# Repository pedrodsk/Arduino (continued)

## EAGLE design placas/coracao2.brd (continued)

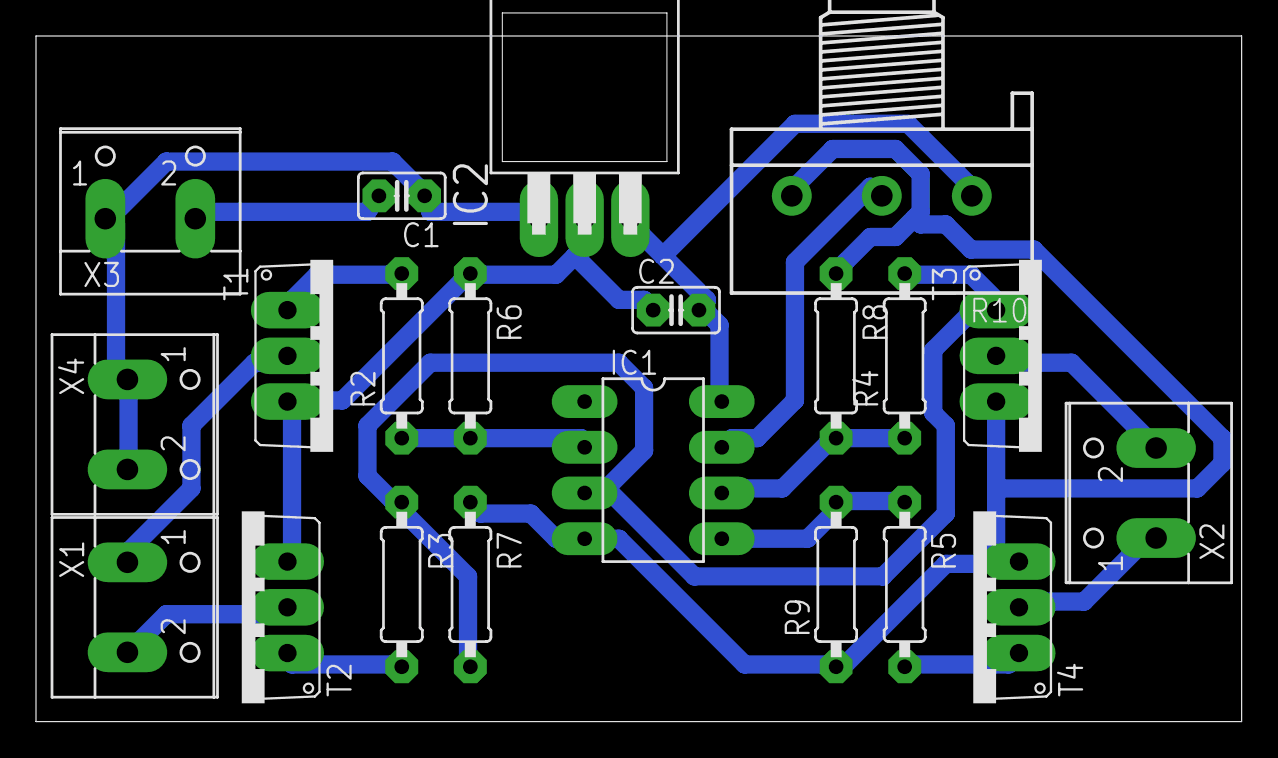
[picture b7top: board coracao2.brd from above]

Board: 1 copper layer, 67.0 x 38.1 mm, 21 parts (0 on the bottom side), 15 nets.

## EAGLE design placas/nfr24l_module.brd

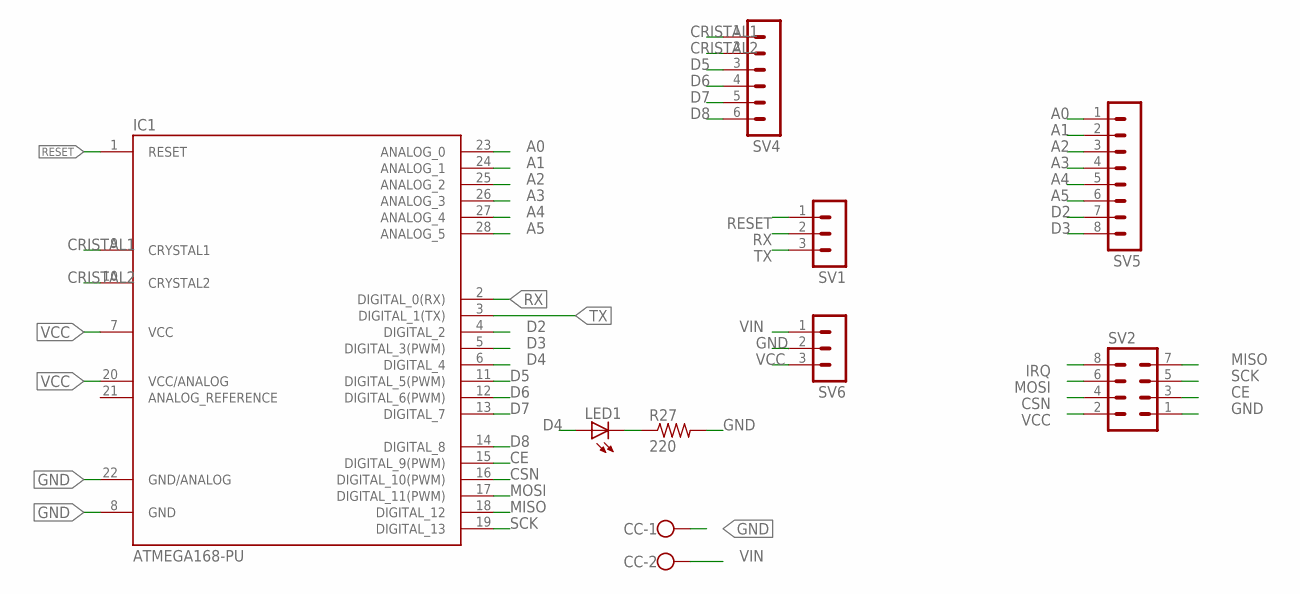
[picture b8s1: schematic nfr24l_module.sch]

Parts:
CC: W237-102
IC1: ATMEGA168-PU; DIL28-3
LED1: LED3MM
R27: 220; 0207/7
SV1, SV6: MA03-1
SV2: MA04-2
SV4: MA06-1
SV5: MA08-1

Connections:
A0: IC1.23 (ANALOG_0), SV5.1
A1: IC1.24 (ANALOG_1), SV5.2
A2: IC1.25 (ANALOG_2), SV5.3
A3: IC1.26 (ANALOG_3), SV5.4
A4: IC1.27 (ANALOG_4), SV5.5
A5: IC1.28 (ANALOG_5), SV5.6
CE: IC1.15 (DIGITAL_9(PWM)), SV2.3
CRISTAL1: IC1.9 (CRYSTAL1), SV4.1
CRISTAL2: IC1.10 (CRYSTAL2), SV4.2
CSN: IC1.16 (DIGITAL_10(PWM)), SV2.4
D2: IC1.4 (DIGITAL_2), SV5.7
D3: IC1.5 (DIGITAL_3(PWM)), SV5.8
D4: IC1.6 (DIGITAL_4), LED1.A
D5: IC1.11 (DIGITAL_5(PWM)), SV4.3
D6: IC1.12 (DIGITAL_6(PWM)), SV4.4
D7: IC1.13 (DIGITAL_7), SV4.5
D8: IC1.14 (DIGITAL_8), SV4.6
GND: CC.1, IC1.8 (GND), IC1.22 (GND/ANALOG), R27.2, SV2.1, SV6.2
IRQ: SV2.8
MISO: IC1.18 (DIGITAL_12), SV2.7
MOSI: IC1.17 (DIGITAL_11(PWM)), SV2.6
unnamed: LED1.K (C), R27.1
RESET: IC1.1 (RESET), SV1.1
RX: IC1.2 (DIGITAL_0(RX)), SV1.2
SCK: IC1.19 (DIGITAL_13), SV2.5
TX: IC1.3 (DIGITAL_1(TX)), SV1.3
VCC: IC1.7 (VCC), IC1.20 (VCC/ANALOG), SV2.2, SV6.3
VIN: CC.2, SV6.1

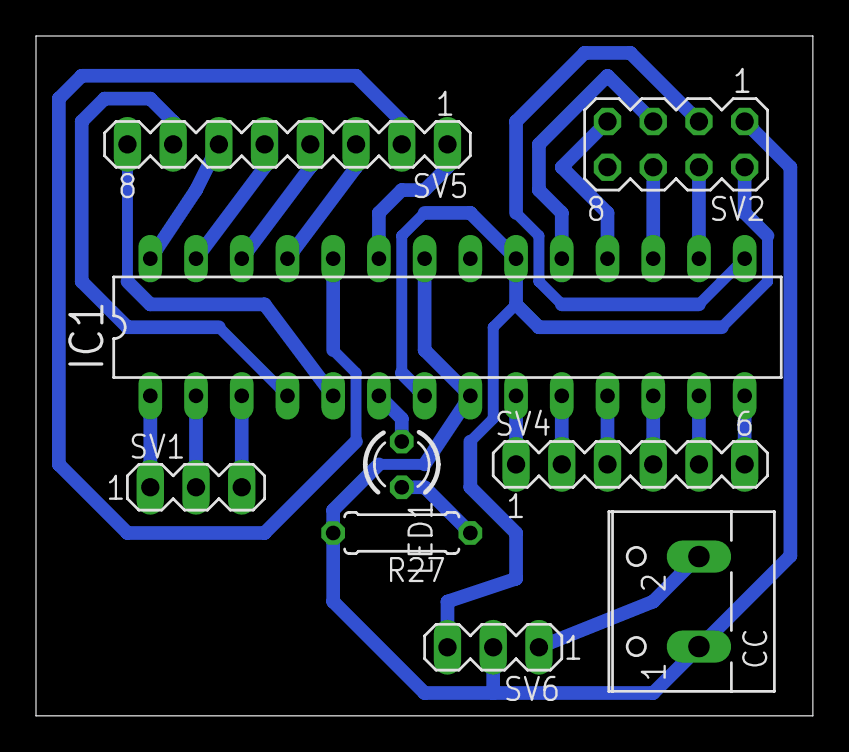
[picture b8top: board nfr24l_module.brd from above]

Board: 2 copper layers, 43.2 x 37.8 mm, 9 parts (0 on the bottom side), 27 nets.

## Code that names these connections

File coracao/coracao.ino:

#define bomba1 2
#define bomba2 4
#define vibra1 3
#define vibra2 5
#define pot 14
#define led 7
//int leitura;
//int converter;
void setup() {
pinMode(bomba1,OUTPUT);
pinMode(bomba2,OUTPUT);
pinMode(vibra1,OUTPUT);
pinMode(vibra2,OUTPUT);
pinMode(led,OUTPUT);
pinMode(pot,INPUT);
Serial.begin(9600);
}

void loop() {
  
int leitura = analogRead(pot);
int converter = map(leitura, 0, 1023, 400, 1200);
int converter2 = map(converter,400,1200,150,50);
//Serial.println(converter2);
Serial.println(leitura);
digitalWrite(vibra1,HIGH);
delay(converter);
analogWrite(vibra1,LOW);
delay(converter);
}

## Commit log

2018-07-04 Projetos Arduino
